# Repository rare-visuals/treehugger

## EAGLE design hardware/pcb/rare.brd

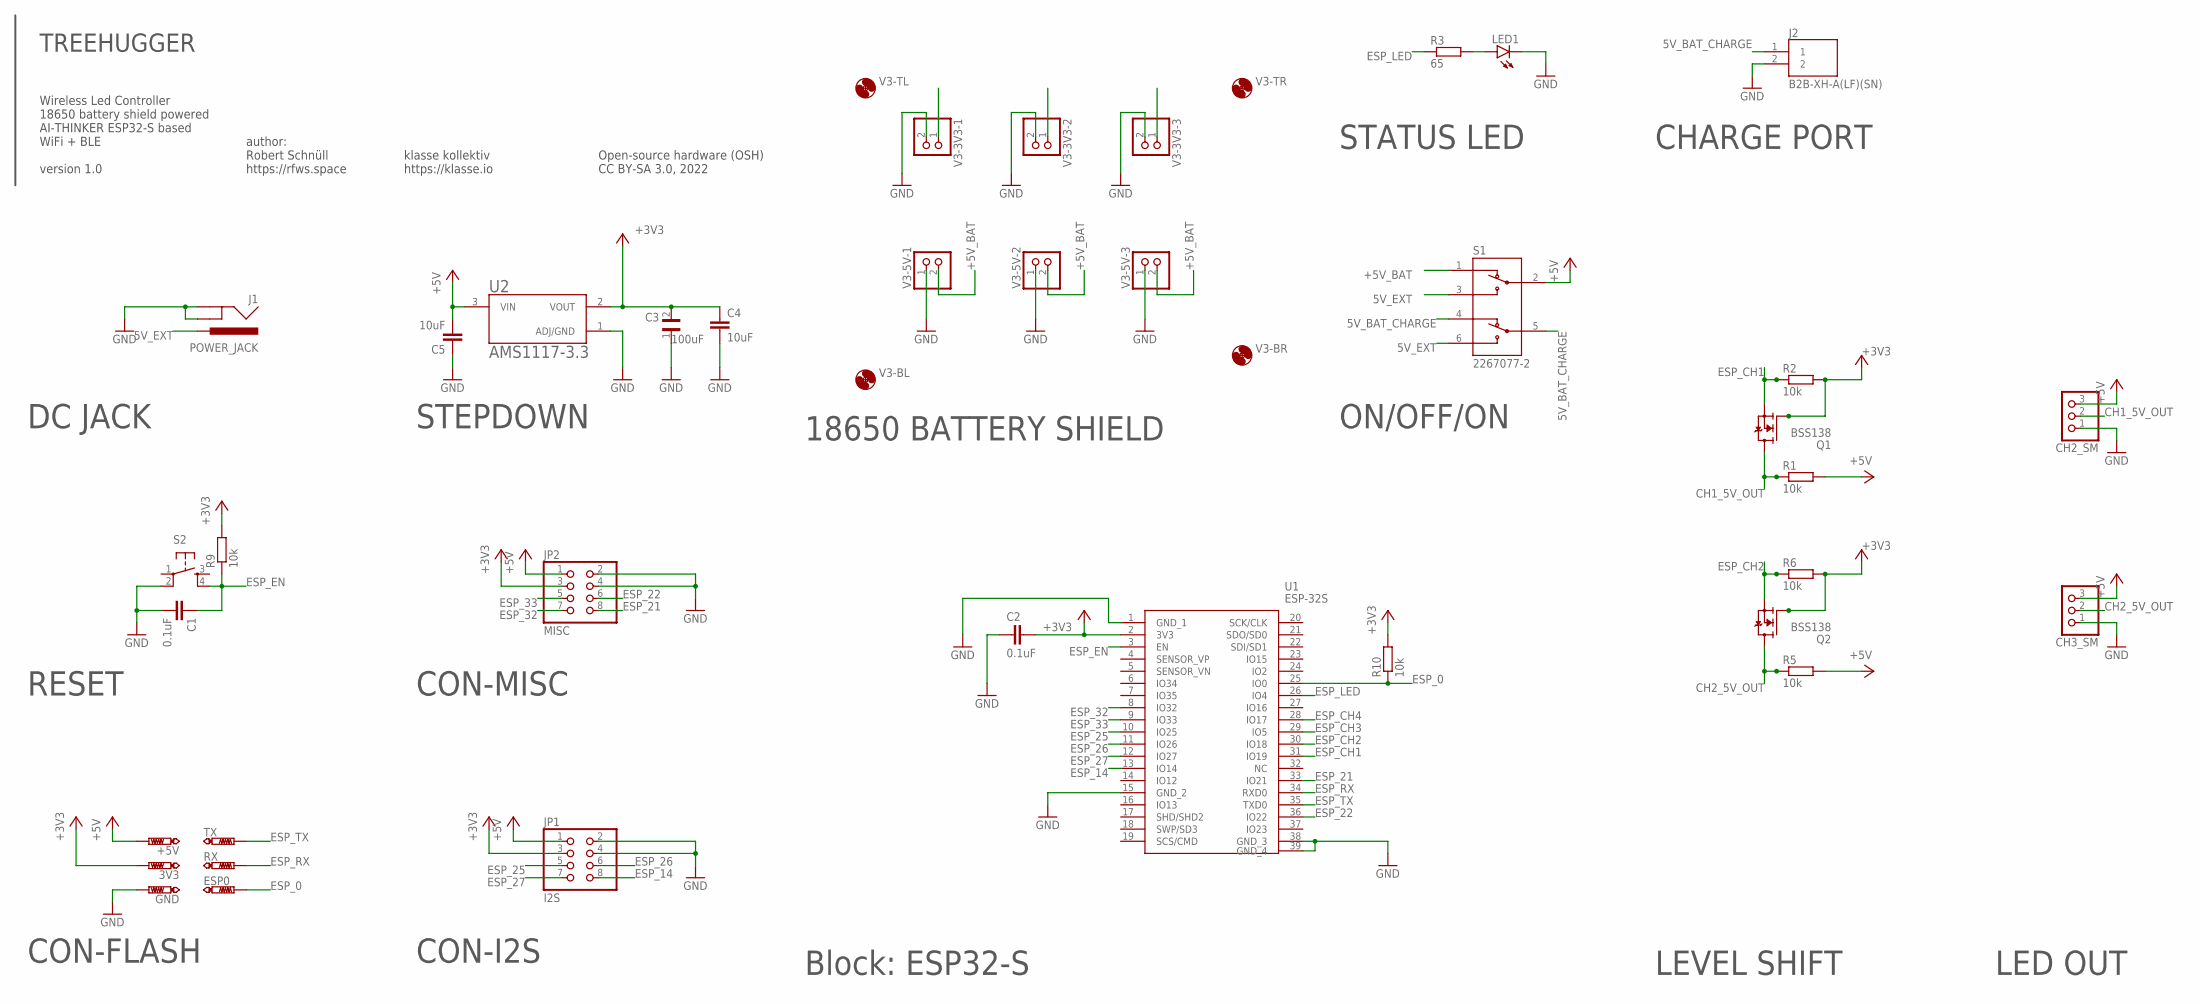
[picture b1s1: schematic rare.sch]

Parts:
3V3: PTR1TP15R; TP15R
+5V: PTR1TP15R; TP15R
C1, C2: 0.1uF; C0805
C3: 100uF; CAPPC3528X210N
C4, C5: 10uF; C0805
CH2_SM, CH3_SM: PINHD-1X3/90; 1X03/90
ESP0: PTR1TP15R; TP15R
GND: PTR1TP15R; TP15R
J1: POWER_JACK; POWER_JACK_PTH
J2: B2B-XH-A(LF)(SN); JST_B2B-XH-A(LF)(SN)
JP1: I2S; 2X04
JP2: MISC; 2X04
LED1: LEDCHIP-LED0805; CHIP-LED0805
Q1, Q2: BSS138; SOT23
R1, R2, R5, R6, R9, R10: 10k; R0805
R3: 65; R0805
RX: PTR1TP15R; TP15R
S1: 2267077-2; TE_2267077-2
S2: TAC_SWITCHSMD; TACTILE_SWITCH_SMD
TX: PTR1TP15R; TP15R
U1: ESP-32S
U2: AMS1117-3.3; SOT229P700X180-4N
V3-3V3-1, V3-3V3-2, V3-3V3-3, V3-5V-1, V3-5V-2, V3-5V-3: PINHD-1X2; 1X02
V3-BL, V3-BR, V3-TL, V3-TR: MOUNT-HOLE3.2; 3,2

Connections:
5V_BAT_CHARGE: J2.1, S1.4, S1.5
5V_EXT: J1.PWR, S1.3, S1.6
+3V3: 3V3.TP, C2.2, C3.2, C4.1, JP1.3, JP2.3, Q1.1 (G), Q2.1 (G), R2.2, R6.2, R9.2, R10.2, U1.2 (3V3), U2.2 (VOUT)
+5V: +5V.TP, C5.2, CH2_SM.3, CH3_SM.3, JP1.1, JP2.1, R1.2, R5.2, S1.2, U2.3 (VIN)
+5V_BAT: S1.1, V3-5V-1.2, V3-5V-2.2, V3-5V-3.2
CH1_5V_OUT: CH2_SM.2, Q1.3 (D), R1.1
CH2_5V_OUT: CH3_SM.2, Q2.3 (D), R5.1
ESP_0: ESP0.TP, R10.1, U1.25 (IO0)
ESP_14: JP1.8, U1.13 (IO14)
ESP_21: JP2.8, U1.33 (IO21)
ESP_22: JP2.6, U1.36 (IO22)
ESP_25: JP1.5, U1.10 (IO25)
ESP_26: JP1.6, U1.11 (IO26)
ESP_27: JP1.7, U1.12 (IO27)
ESP_32: JP2.7, U1.8 (IO32)
ESP_33: JP2.5, U1.9 (IO33)
ESP_CH1: Q1.2 (S), R2.1, U1.31 (IO19)
ESP_CH2: Q2.2 (S), R6.1, U1.30 (IO18)
ESP_CH3: U1.29 (IO5)
ESP_CH4: U1.28 (IO17)
ESP_EN: C1.1, R9.1, S2.4, U1.3 (EN)
ESP_LED: R3.1, U1.26 (IO4)
ESP_RX: RX.TP, U1.34 (RXD0)
ESP_TX: TX.TP, U1.35 (TXD0)
GND: C1.2, C2.1, C3.1, C4.2, C5.1, CH2_SM.1, CH3_SM.1, GND.TP, J1.GND, J1.GNDBREAK, J2.2, JP1.2, JP1.4, JP2.2, JP2.4, LED1.C, S2.2, U1.1 (GND_1), U1.15 (GND_2), U1.38 (GND_3), U1.39 (GND_4), U2.1 (ADJ/GND), V3-3V3-1.2, V3-3V3-2.2, V3-3V3-3.2, V3-5V-1.1, V3-5V-2.1, V3-5V-3.1
unnamed: LED1.A, R3.2

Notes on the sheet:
Block: ESP32-S
Wireless Led Controller 18650 battery shield powered AI-THINKER ESP32-S based WiFi + BLE version 1.0
TREEHUGGER
CON-I2S
CON-MISC
LEVEL SHIFT
LED OUT
CON-FLASH
18650 BATTERY SHIELD
RESET
DC JACK
STEPDOWN
ON/OFF/ON
author: Robert Schnüll https://rfws.space
Open-source hardware (OSH) CC BY-SA 3.0, 2022
klasse kollektiv https://klasse.io
STATUS LED
CHARGE PORT

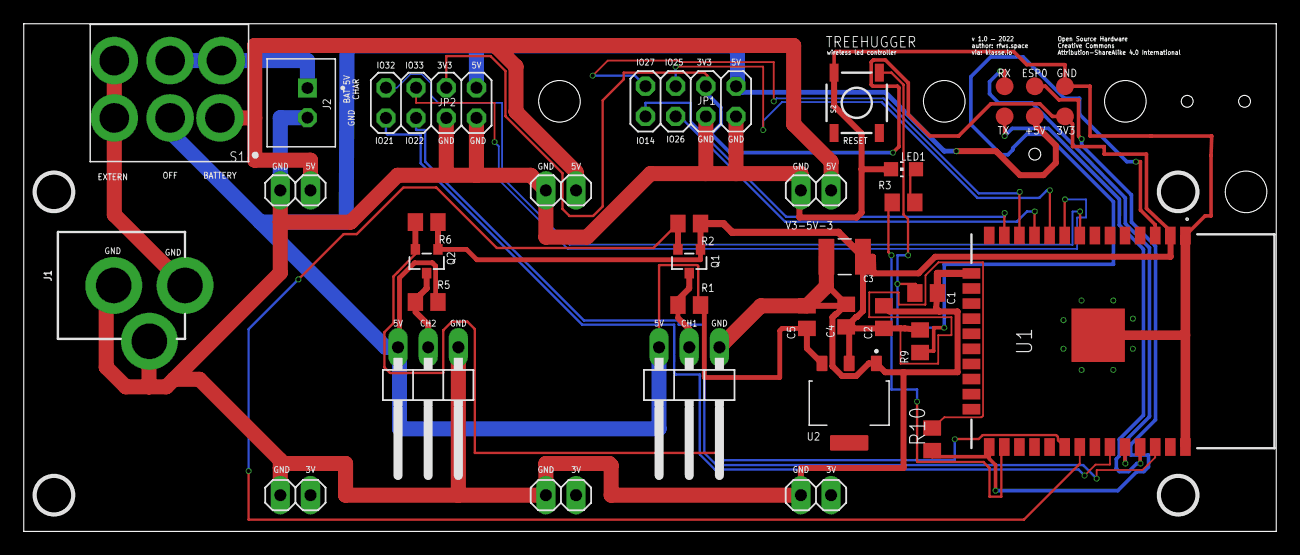
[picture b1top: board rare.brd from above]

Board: 2 copper layers, 105.4 x 42.7 mm, 41 parts (0 on the bottom side), 24 nets.

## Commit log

2022-11-06 Initial firmware commit
2022-11-06 initial commit pcb
2022-11-06 initial case commit

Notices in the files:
hardware/pcb/rare.brd:
Creative Commons
Attribution-ShareAlike 4.0 International
parts and their libraries:
SparkFun-Connectors: Licensing: Creative Commons ShareAlike 4.0 International - https://creativecommons.org/licenses/by-sa/4.0
